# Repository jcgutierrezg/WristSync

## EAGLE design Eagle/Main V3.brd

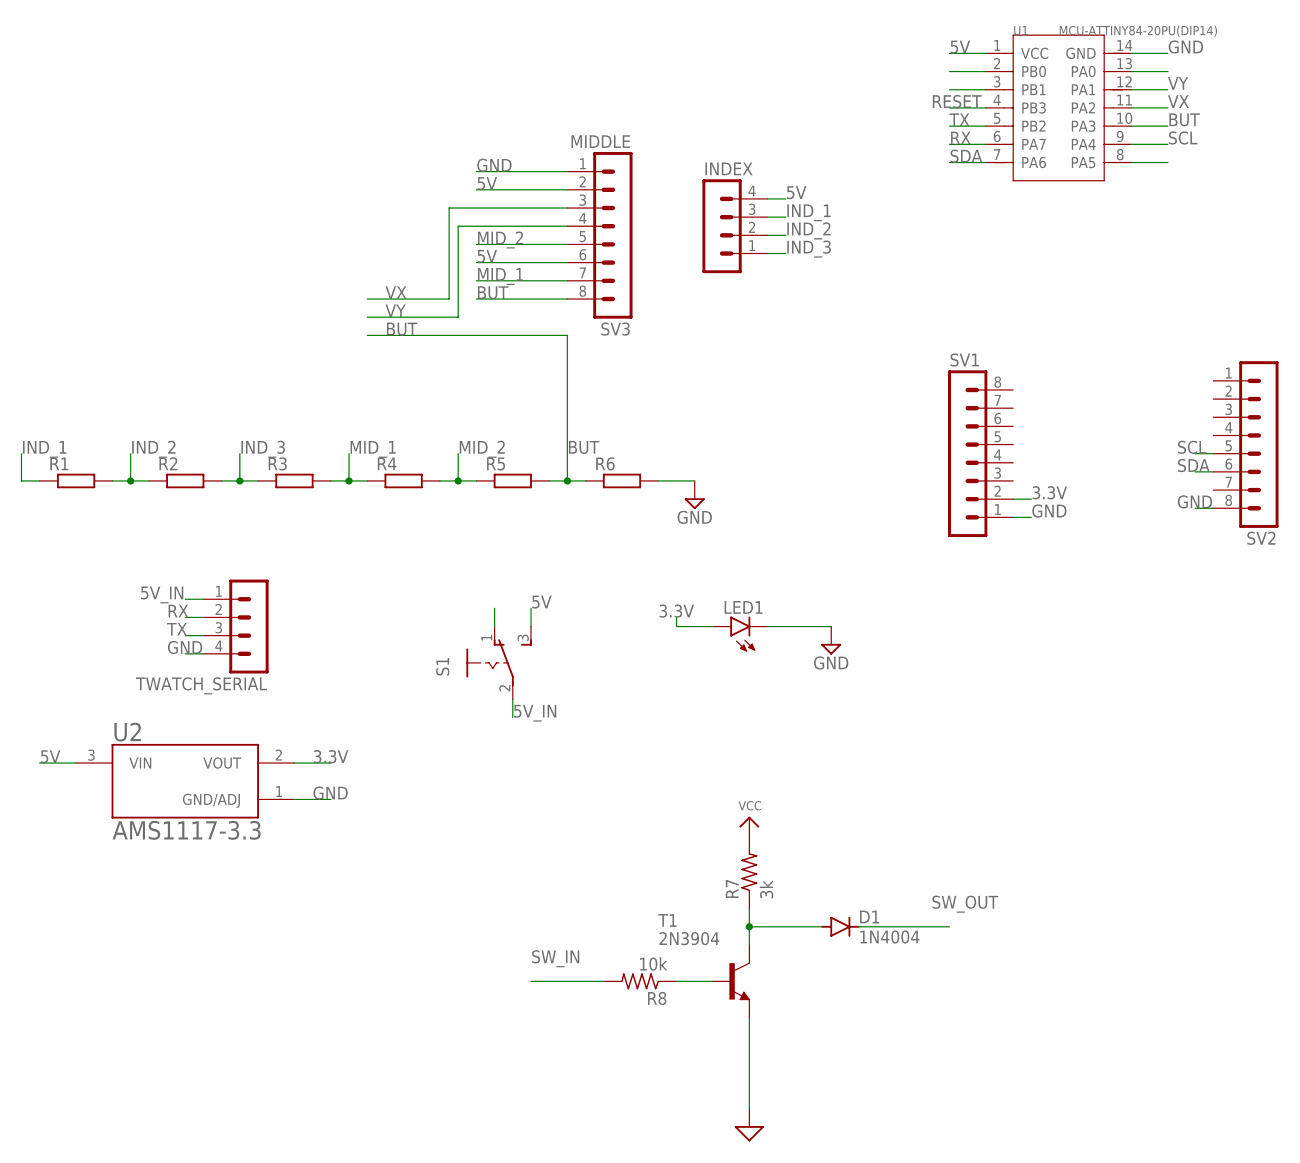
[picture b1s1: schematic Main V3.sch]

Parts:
D1: 1N4004; DO41-10
INDEX: MA04-1
LED1: LED5MM
R1, R2, R3, R4, R5, R6: R-EU_0204/7; 0204/7
R7: 3k; 0204/5
R8: 10k; 0204/5
S1: 255SB
SV1, SV2: MA08-1
SV3: MIDDLE; MA08-1
T1: 2N3904; TO92
TWATCH_SERIAL: MA04-1
U1: MCU-ATTINY84-20PU(DIP14); DIP14-2.54-17.24X6.35MM
U2: AMS1117-3.3; SOT229P700X180-4N

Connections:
3.3V: LED1.A, SV1.2, U2.2 (VOUT)
5V: INDEX.4, S1.3 (S), SV3.2, SV3.6, U1.1 (VCC), U2.3 (VIN)
5V_IN: S1.2, TWATCH_SERIAL.1
BUT: R5.2, R6.1, SV3.8, U1.10 (PA3)
GND: LED1.K (C), R6.2, SV1.1, SV2.8, SV3.1, T1.3 (E), TWATCH_SERIAL.4, U1.14 (GND), U2.1 (GND/ADJ)
IND_1: INDEX.3, R1.1
IND_2: INDEX.2, R1.2, R2.1
IND_3: INDEX.1, R2.2, R3.1
MID_1: R3.2, R4.1, SV3.7
MID_2: R4.2, R5.1, SV3.5
unnamed: R8.1, T1.2 (B)
unnamed: D1.A, R7.1, T1.1 (C)
RESET: U1.4 (PB3)
RX: TWATCH_SERIAL.2, U1.6 (PA7)
SCL: SV2.5, U1.9 (PA4)
SDA: SV2.6, U1.7 (PA6)
SW_IN: R8.2
SW_OUT: D1.C
TX: TWATCH_SERIAL.3, U1.5 (PB2)
VCC: R7.2
VX: SV3.3, U1.11 (PA2)
VY: SV3.4, U1.12 (PA1)

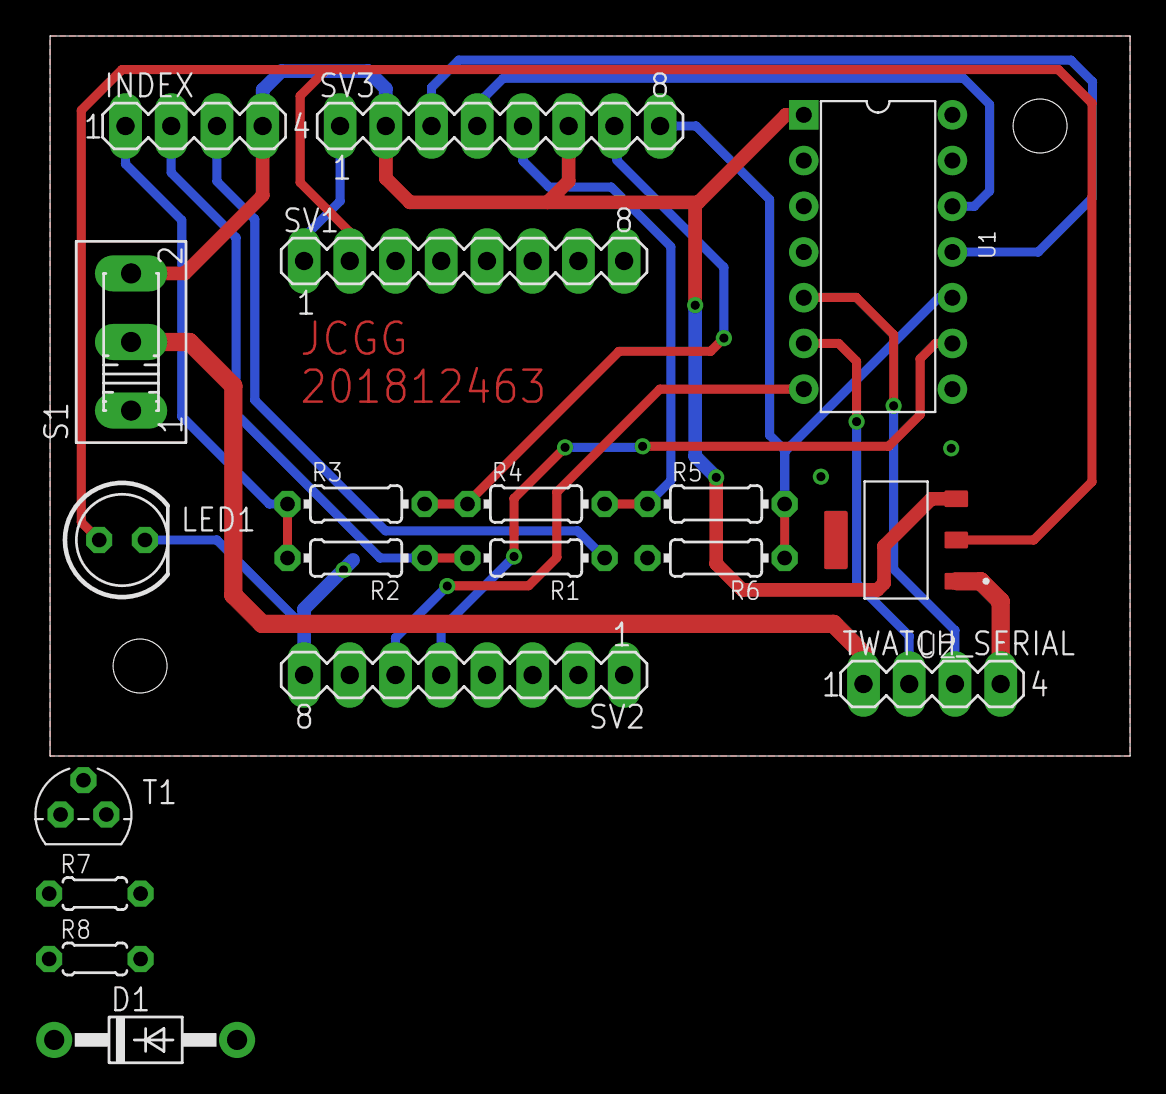
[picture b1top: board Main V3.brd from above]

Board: 2 copper layers, 60.0 x 40.0 mm, 19 parts (0 on the bottom side), 18 nets.

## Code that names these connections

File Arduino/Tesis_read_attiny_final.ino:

#include <TinyWireM.h>
#include <SendOnlySoftwareSerial.h>

const int Tx = 7; //SoftwareSerial TX

SendOnlySoftwareSerial SWSerial(Tx);

int16_t AcX, AcY, AcZ, GyX, GyY, GyZ, MgX, MgY, MgZ; //MSB 8bit RAW values from the MPU
double AcX_Out, AcY_Out, AcZ_Out, GyX_Out, GyY_Out, GyZ_Out, MgX_Out, MgY_Out, MgZ_Out; //Output processed values accounting sensitivity settings

const int AccGyr_CLICK = 0x6A; // I2C address of the MPU-9250
const int Mag_CLICK = 0x1C;

double elapsedTime, currentTime, previousTime;

const double maxRes = 32768;

const int macroSens = 0;
double scale_G = 0;
double LSB_G = 0;
double scale_A = 0;
double LSB_A = 0;
double scale_M = 0;
double LSB_M = 0;

const int buttonRange = 5;

int joyX, joyY, buttons;

int activeBut = 0;

const int IND_1 = 256;
const int IND_2 = 204;
const int IND_3 = 170;

const int MID_1 = 1023;
const int MID_2 = 162;
const int MID_3 = 341;

void setup() {
  SWSerial.begin(38400);

  delay(2000);

  TinyWireM.begin(); // sda, scl, clock speed

  pinMode(1, INPUT);
  pinMode(2, INPUT);
  pinMode(3, INPUT);

  initiate_IMU_CLICK(); //4%

}

void loop() {

  readSensor_CLICK(); //12%
  readAnalogs(); //1%

  previousTime = currentTime;

  currentTime = millis();

  elapsedTime = currentTime - previousTime;

  //  SWSerial.print(elapsedTime);
  //  SWSerial.print(", ");

  SWSerial.print(AcX_Out);
  SWSerial.print(";");
  SWSerial.print(AcY_Out);
  SWSerial.print(";");
  SWSerial.print(AcZ_Out);
  SWSerial.print(";");
  SWSerial.print(GyX_Out);
  SWSerial.print(";");
  SWSerial.print(GyY_Out);
  SWSerial.print(";");
  SWSerial.print(GyZ_Out);
  SWSerial.print(";");
  SWSerial.print(MgX_Out);
  SWSerial.print(";");
  SWSerial.print(MgY_Out);
  SWSerial.print(";");
  SWSerial.print(MgZ_Out);
  SWSerial.print(";");
  SWSerial.print(joyX);
  SWSerial.print(";");
  SWSerial.print(joyY);
  SWSerial.print(";");
  SWSerial.print(activeBut);
  SWSerial.print(";");
  SWSerial.print(elapsedTime);
  SWSerial.println(";");
  //  SWSerial.print(buttons);
  //  SWSerial.println(";");


}

void initiate_IMU_CLICK()
{

  //SENSITIVITY SET FOR MPU

  TinyWireM.beginTransmission(AccGyr_CLICK);
  TinyWireM.write(0x10);  // GYRO_CONFIG register

#if macroSens == 0
  TinyWireM.write(0b01000000); // Bit 3,4: 0 -> ±245 °/s, 133.75 LSB/°/s
  scale_G = 245;
#elif macroSens == 1
  TinyWireM.write(0b01001000); // Bit 3,4: 1 -> ±500 °/s, 65.5 LSB/°/s
  scale_G = 500;
#elif (macroSens == 2 || macroSens == 3)
  TinyWireM.write(0b01011000); // Bit 3,4: 2/3 -> ±2000 °/s, 16.38 LSB/°/s
  scale_G = 2000;
#else
  TinyWireM.write(0b01000000); // Default: Bit 3,4: 0 -> ±245 °/s, 133.75 LSB/°/s
  scale_G = 245;
#endif

  LSB_G = maxRes / scale_G;
  TinyWireM.endTransmission(true);

  TinyWireM.beginTransmission(AccGyr_CLICK);
  TinyWireM.write(0x20);  // ACCEL_CONFIG register

#if macroSens == 0
  TinyWireM.write(0b00000000); // Bit 3,4: 0 -> ±2g, 16384 LSB/g
  scale_A = 2;
#elif macroSens == 1
  TinyWireM.write(0b00001000); // Bit 3,4: 1 -> ±4g, 8192 LSB/g
  scale_A = 4;
#elif macroSens == 2
  TinyWireM.write(0b00010000); // Bit 3,4: 2 -> ±8g, 4096 LSB/g
  scale_A = 8;
#elif macroSens == 3
  TinyWireM.write(0b00011000); // Bit 3,4: 3 -> ±16g, 2048 LSB/g
  scale_A = 16;
#else
  TinyWireM.write(0b00000000); // Bit 3,4: 0 -> ±2g, 16384 LSB/g
  scale_A = 2;
#endif

  LSB_A = maxRes / scale_A;
  TinyWireM.endTransmission(true);

  TinyWireM.beginTransmission(Mag_CLICK);
  TinyWireM.write(0x21);  // MAGN_CONFIG register

#if macroSens == 0
  TinyWireM.write(0b00000000); // Bit 5,6: 0 -> ±4G, 8192 LSB/G
  scale_M = 4;
#elif macroSens == 1
  TinyWireM.write(0b00100000); // Bit 5,6: 1 -> ±8G, 4096 LSB/G
  scale_M = 8;
#elif macroSens == 2
  TinyWireM.write(0b01000000); // Bit 5,6: 2 -> ±12G, 2730.66 LSB/G
  scale_M = 12;
#elif macroSens == 3
  TinyWireM.write(0b01100000); // Bit 5,6: 3 -> ±16G, 2048 LSB/G
  scale_M = 16;
#else
  TinyWireM.write(0b01000000); // Bit 3,4: 0 -> ±2g, 8192 LSB/G
  scale_M = 4;
#endif

  LSB_M = maxRes / scale_M;
  TinyWireM.endTransmission(true);

  TinyWireM.beginTransmission(Mag_CLICK);
  TinyWireM.write(0x22);
  TinyWireM.write(0b00000000);
  TinyWireM.endTransmission(true);
}

void readSensor_CLICK()
{
  TinyWireM.beginTransmission(AccGyr_CLICK);
  TinyWireM.write(0x28);
  TinyWireM.endTransmission(true);
  TinyWireM.requestFrom(AccGyr_CLICK, 6);

  AcX = TinyWireM.read();
  AcX_Out = (AcX | (TinyWireM.read() << 8)) / LSB_A;
  AcY = TinyWireM.read();
  AcY_Out = (AcY | (TinyWireM.read() << 8)) / LSB_A;
  AcZ = TinyWireM.read();
  AcZ_Out = (AcZ | (TinyWireM.read() << 8)) / LSB_A;

  TinyWireM.beginTransmission(AccGyr_CLICK);
  TinyWireM.write(0x18);
  TinyWireM.endTransmission(true);
  TinyWireM.requestFrom(AccGyr_CLICK, 6);

  GyX = TinyWireM.read();
  GyX_Out = (GyX | (TinyWireM.read() << 8)) / LSB_G;
  GyY = TinyWireM.read();
  GyY_Out = (GyY | (TinyWireM.read() << 8)) / LSB_G;
  GyZ = TinyWireM.read();
  GyZ_Out = (GyZ | (TinyWireM.read() << 8)) / LSB_G;

  TinyWireM.beginTransmission(Mag_CLICK);
  TinyWireM.write(0x28);
  TinyWireM.endTransmission(true);
  TinyWireM.requestFrom(Mag_CLICK, 6);

  MgX = TinyWireM.read();
  MgX_Out = (MgX | (TinyWireM.read() << 8)) / LSB_M;
  MgY = TinyWireM.read();
  MgY_Out = (MgY | (TinyWireM.read() << 8)) / LSB_M;
  MgZ = TinyWireM.read();
  MgZ_Out = (MgZ | (TinyWireM.read() << 8)) / LSB_M;
}

void readAnalogs()
{
  joyX = analogRead(2);
  joyY = analogRead(1);

  buttons = analogRead(3);

  if (buttons <= IND_1 + buttonRange and buttons >= IND_1 - buttonRange)
  {
    activeBut = 1;
  }
  else if (buttons <= IND_2 + buttonRange and buttons >= IND_2 - buttonRange)
  {
    activeBut = 2;
  }
  else if (buttons <= IND_3 + buttonRange and buttons >= IND_3 - buttonRange)
  {
    activeBut = 3;
  }
  else if (buttons <=  MID_1 + buttonRange and buttons >= MID_1 - buttonRange)
  {
    activeBut = 4;
  }
  else if (buttons <= MID_2 + buttonRange and buttons >= MID_2 - buttonRange)
  {
    activeBut = 5;
  }
  else if (buttons <= MID_3 + buttonRange and buttons >= MID_3 - buttonRange)
  {
    activeBut = 6;
  }
  else
  {
    activeBut = 0;
  }

}
